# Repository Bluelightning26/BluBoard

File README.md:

# BluBoard
## A custom 75% keyboard!

### Key features: 
- MacOs Layout, 75% & separated arrow keys
- Two Rotary Encoders w/ Switches (Brightness + Volume)
- Cherry MX Brown Switches
- Simple Case with plop in design that keeps the black PCB visible while protecting the bottom and sides
- Specific parts used are documented in [BOM.md](BOM.md)

## Renders!!

### What I'd do differently next time
There were several sacrifices I had to make in the name of budgeting. Also, since this is my first full keyboard, I didn't want to overwhelm myself in the build process and avoided things that are difficult to solder. I am planning on making a v2 version of this keyboard after a few months of use, learning from the probable mistakes I made in design along the way

Nice features this would have:
- Wireless capability, BT + Dongle
- Acrylic Case
- RGB Backlit Keys
- 
(To be added to during build process along with when I use the board!)

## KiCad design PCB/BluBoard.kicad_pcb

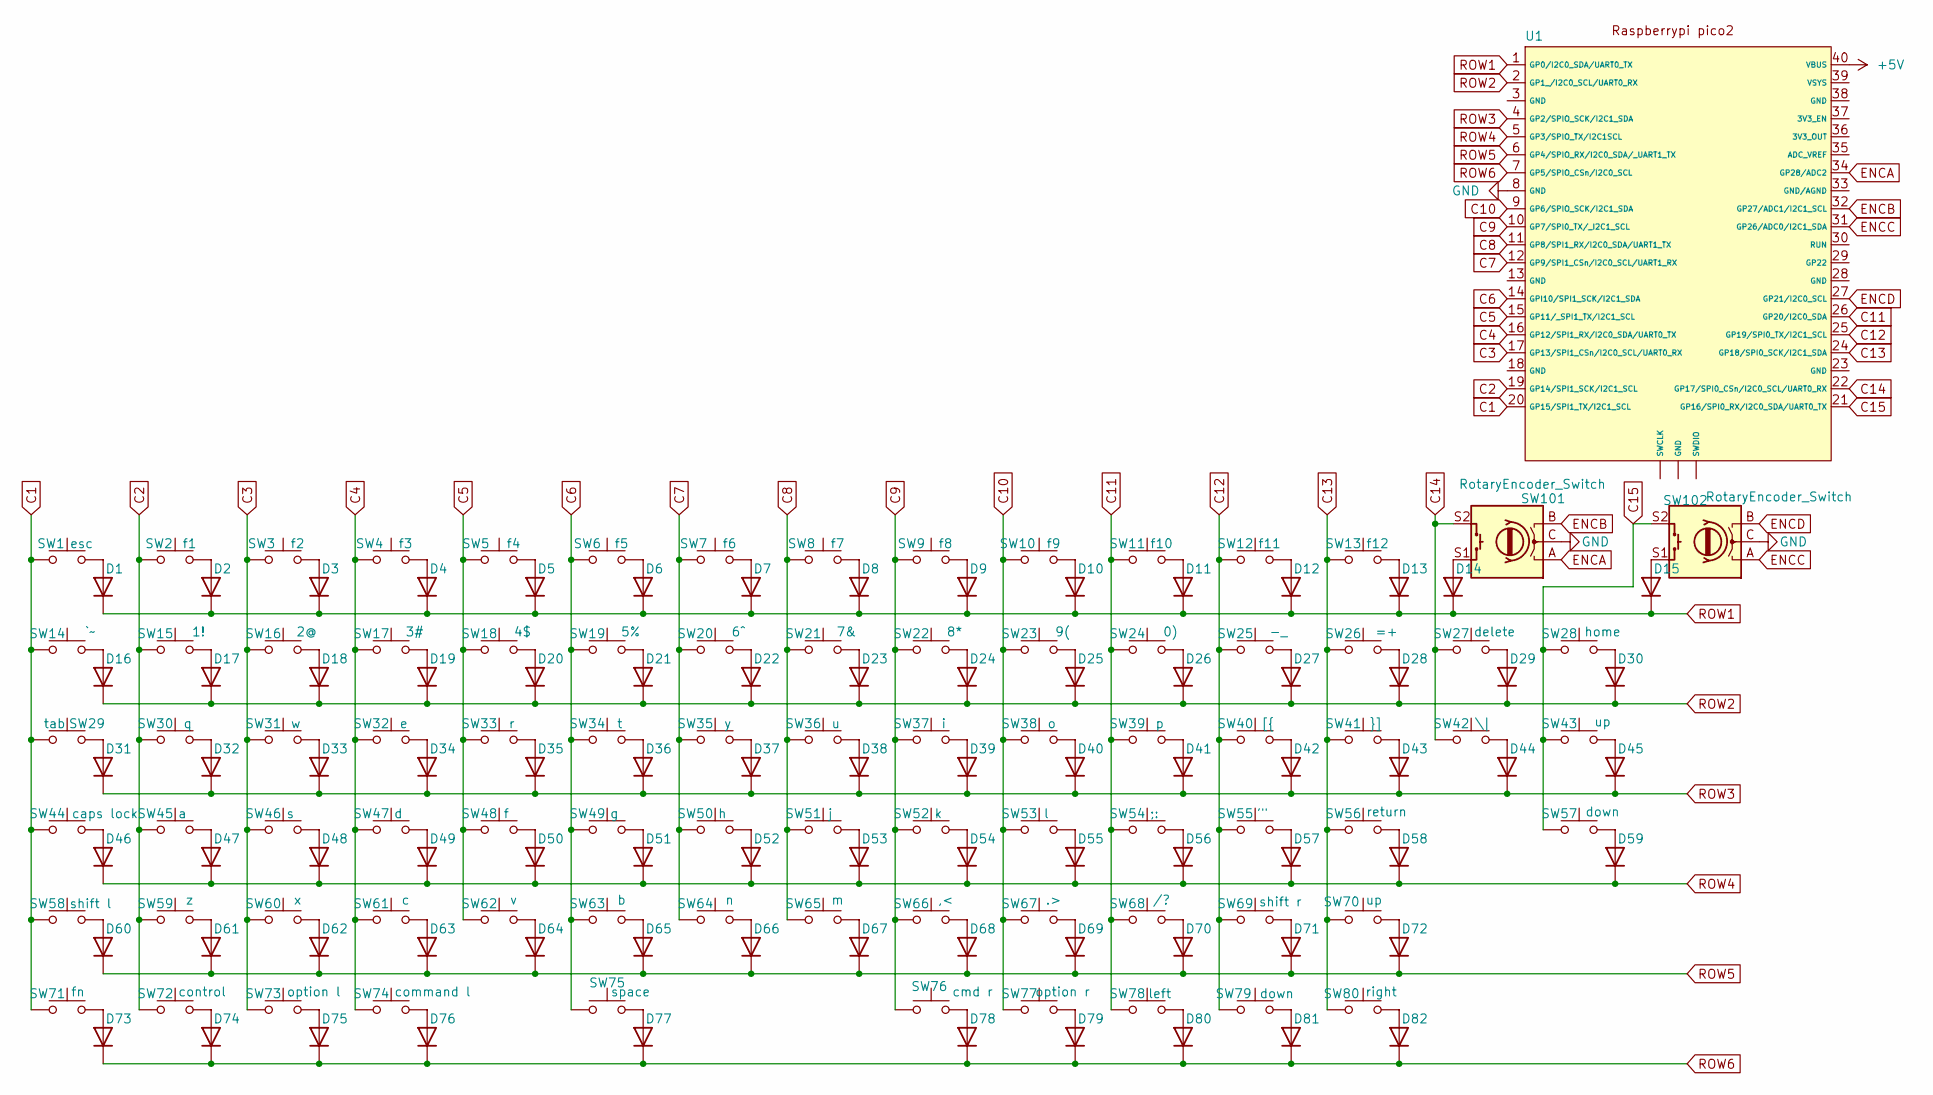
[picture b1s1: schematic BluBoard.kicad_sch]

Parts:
D1, D2, D3, D4, D5, D6, D7, D8, D9, D10, D11, D12, D13, D14, D15, D16, D17, D18, D19, D20, D21, D22, D23, D24, D25, D26, D27, D28, D29, D30, D31, D32, D33, D34, D35, D36, D37, D38, D39, D40, D41, D42, D43, D44, D45, D46, D47, D48, D49, D50, D51, D52, D53, D54, D55, D56, D57, D58, D59, D60, D61, D62, D63, D64, D65, D66, D67, D68, D69, D70, D71, D72, D73, D74, D75, D76, D77, D78, D79, D80, D81, D82: D; D_DO-35_SOD27_P7.62mm_Horizontal
SW1: esc; SW_Cherry_MX_1.00u_PCB
SW2: f1; SW_Cherry_MX_1.00u_PCB
SW3: f2; SW_Cherry_MX_1.00u_PCB
SW4: f3; SW_Cherry_MX_1.00u_PCB
SW5: f4; SW_Cherry_MX_1.00u_PCB
SW6: f5; SW_Cherry_MX_1.00u_PCB
SW7: f6; SW_Cherry_MX_1.00u_PCB
SW8: f7; SW_Cherry_MX_1.00u_PCB
SW9: f8; SW_Cherry_MX_1.00u_PCB
SW10: f9; SW_Cherry_MX_1.00u_PCB
SW11: f10; SW_Cherry_MX_1.00u_PCB
SW12: f11; SW_Cherry_MX_1.00u_PCB
SW13: f12; SW_Cherry_MX_1.00u_PCB
SW14: `~; SW_Cherry_MX_1.00u_PCB
SW15: 1!; SW_Cherry_MX_1.00u_PCB
SW16: 2@; SW_Cherry_MX_1.00u_PCB
SW17: 3#; SW_Cherry_MX_1.00u_PCB
SW18: 4$; SW_Cherry_MX_1.00u_PCB
SW19: 5%; SW_Cherry_MX_1.00u_PCB
SW20: 6^; SW_Cherry_MX_1.00u_PCB
SW21: 7&; SW_Cherry_MX_1.00u_PCB
SW22: 8*; SW_Cherry_MX_1.00u_PCB
SW23: 9(; SW_Cherry_MX_1.00u_PCB
SW24: 0); SW_Cherry_MX_1.00u_PCB
SW25: -_; SW_Cherry_MX_1.00u_PCB
SW26: =+; SW_Cherry_MX_1.00u_PCB
SW27: delete; SW_Cherry_MX_2.00u_PCB
SW28: home; SW_Cherry_MX_1.00u_PCB
SW29: tab; SW_Cherry_MX_1.50u_PCB
SW30: q; SW_Cherry_MX_1.00u_PCB
SW31: w; SW_Cherry_MX_1.00u_PCB
SW32: e; SW_Cherry_MX_1.00u_PCB
SW33: r; SW_Cherry_MX_1.00u_PCB
SW34: t; SW_Cherry_MX_1.00u_PCB
SW35: y; SW_Cherry_MX_1.00u_PCB
SW36: u; SW_Cherry_MX_1.00u_PCB
SW37: i; SW_Cherry_MX_1.00u_PCB
SW38: o; SW_Cherry_MX_1.00u_PCB
SW39: p; SW_Cherry_MX_1.00u_PCB
SW40: [{; SW_Cherry_MX_1.00u_PCB
SW41: }]; SW_Cherry_MX_1.00u_PCB
SW42: \|; SW_Cherry_MX_1.50u_PCB
SW43, SW70: up; SW_Cherry_MX_1.00u_PCB
SW44: caps lock; SW_Cherry_MX_1.75u_PCB
SW45: a; SW_Cherry_MX_1.00u_PCB
SW46: s; SW_Cherry_MX_1.00u_PCB
SW47: d; SW_Cherry_MX_1.00u_PCB
SW48: f; SW_Cherry_MX_1.00u_PCB
SW49: g; SW_Cherry_MX_1.00u_PCB
SW50: h; SW_Cherry_MX_1.00u_PCB
SW51: j; SW_Cherry_MX_1.00u_PCB
SW52: k; SW_Cherry_MX_1.00u_PCB
SW53: l; SW_Cherry_MX_1.00u_PCB
SW54: ;:; SW_Cherry_MX_1.00u_PCB
SW55: '"; SW_Cherry_MX_1.00u_PCB
SW56: return; SW_Cherry_MX_2.25u_PCB
SW57, SW79: down; SW_Cherry_MX_1.00u_PCB
SW58: shift l; SW_Cherry_MX_2.25u_PCB
SW59: z; SW_Cherry_MX_1.00u_PCB
SW60: x; SW_Cherry_MX_1.00u_PCB
SW61: c; SW_Cherry_MX_1.00u_PCB
SW62: v; SW_Cherry_MX_1.00u_PCB
SW63: b; SW_Cherry_MX_1.00u_PCB
SW64: n; SW_Cherry_MX_1.00u_PCB
SW65: m; SW_Cherry_MX_1.00u_PCB
SW66: ,<; SW_Cherry_MX_1.00u_PCB
SW67: .>; SW_Cherry_MX_1.00u_PCB
SW68: /?; SW_Cherry_MX_1.00u_PCB
SW69: shift r; SW_Cherry_MX_2.25u_PCB
SW71: fn; SW_Cherry_MX_1.00u_PCB
SW72: control; SW_Cherry_MX_1.00u_PCB
SW73: option l; SW_Cherry_MX_1.00u_PCB
SW74: command l; SW_Cherry_MX_1.25u_PCB
SW75: space; SW_Cherry_MX_6.25u_PCB
SW76: cmd r; SW_Cherry_MX_1.25u_PCB
SW77: option r; SW_Cherry_MX_1.00u_PCB
SW78: left; SW_Cherry_MX_1.00u_PCB
SW80: right; SW_Cherry_MX_1.00u_PCB
SW101, SW102: RotaryEncoder_Switch; RotaryEncoder_Alps_EC11E-Switch_Vertical_H20mm
U1: RaspberryPi_Pico_Common_THT

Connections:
+5V: U1.40 (VBUS)
C1: SW1.1, SW14.1, SW29.2, SW44.1, SW58.1, SW71.1, U1.20 (GP15/SPI1_TX/I2C1_SCL)
C2: SW2.1, SW15.1, SW30.1, SW45.1, SW59.1, SW72.1, U1.19 (GP14/SPI1_SCK/I2C1_SCL)
C3: SW3.1, SW16.1, SW31.1, SW46.1, SW60.1, SW73.1, U1.17 (GP13/SPI1_CSn/I2C0_SCL/UART0_RX)
C4: SW4.1, SW17.1, SW32.1, SW47.1, SW61.1, SW74.1, U1.16 (GP12/SPI1_RX/I2C0_SDA/UART0_TX)
C5: SW5.1, SW18.1, SW33.1, SW48.1, SW62.1, U1.15 (GP11/_SPI1_TX/I2C1_SCL)
C6: SW6.1, SW19.1, SW34.1, SW49.1, SW63.1, SW75.1, U1.14 (GPI10/SPI1_SCK/I2C1_SDA)
C7: SW7.1, SW20.1, SW35.1, SW50.1, SW64.1, U1.12 (GP9/SPI1_CSn/I2C0_SCL/UART1_RX)
C8: SW8.1, SW21.1, SW36.1, SW51.1, SW65.1, U1.11 (GP8/SPI1_RX/I2C0_SDA/UART1_TX)
C9: SW9.1, SW22.1, SW37.1, SW52.1, SW66.1, SW76.1, U1.10 (GP7/SPI0_TX/_I2C1_SCL)
C10: SW10.1, SW23.1, SW38.1, SW53.1, SW67.1, SW77.1, U1.9 (GP6/SPIO_SCK/I2C1_SDA)
C11: SW11.1, SW24.1, SW39.1, SW54.1, SW68.1, SW78.1, U1.26 (GP20/I2C0_SDA)
C12: SW12.1, SW25.1, SW40.1, SW55.1, SW69.1, SW79.1, U1.25 (GP19/SPI0_TX/I2C1_SCL)
C13: SW13.1, SW26.1, SW41.1, SW56.1, SW70.1, SW80.1, U1.24 (GP18/SPI0_SCK/I2C1_SDA)
C14: SW27.1, SW42.1, SW101.S2, U1.22 (GP17/SPI0_CSn/I2C0_SCL/UART0_RX)
C15: SW28.1, SW43.1, SW57.1, SW102.S2, U1.21 (GP16/SPI0_RX/I2C0_SDA/UART0_TX)
ENCA: SW101.A, U1.34 (GP28/ADC2)
ENCB: SW101.B, U1.32 (GP27/ADC1/I2C1_SCL)
ENCC: SW102.A, U1.31 (GP26/ADC0/I2C1_SDA)
ENCD: SW102.B, U1.27 (GP21/I2C0_SCL)
GND: SW101.C, SW102.C, U1.8 (GND)
unnamed: D1.2 (A), SW1.2
unnamed: D2.2 (A), SW2.2
unnamed: D3.2 (A), SW3.2
unnamed: D4.2 (A), SW4.2
unnamed: D5.2 (A), SW5.2
unnamed: D6.2 (A), SW6.2
unnamed: D7.2 (A), SW7.2
unnamed: D8.2 (A), SW8.2
unnamed: D9.2 (A), SW9.2
unnamed: D10.2 (A), SW10.2
unnamed: D11.2 (A), SW11.2
unnamed: D12.2 (A), SW12.2
unnamed: D13.2 (A), SW13.2
unnamed: D14.2 (A), SW101.S1
unnamed: D15.2 (A), SW102.S1
unnamed: D16.2 (A), SW14.2
unnamed: D17.2 (A), SW15.2
unnamed: D18.2 (A), SW16.2
unnamed: D19.2 (A), SW17.2
unnamed: D20.2 (A), SW18.2
unnamed: D21.2 (A), SW19.2
unnamed: D22.2 (A), SW20.2
unnamed: D23.2 (A), SW21.2
unnamed: D24.2 (A), SW22.2
unnamed: D25.2 (A), SW23.2
unnamed: D26.2 (A), SW24.2
unnamed: D27.2 (A), SW25.2
unnamed: D28.2 (A), SW26.2
unnamed: D29.2 (A), SW27.2
unnamed: D30.2 (A), SW28.2
unnamed: D31.2 (A), SW29.1
unnamed: D32.2 (A), SW30.2
unnamed: D33.2 (A), SW31.2
unnamed: D34.2 (A), SW32.2
unnamed: D35.2 (A), SW33.2
unnamed: D36.2 (A), SW34.2
unnamed: D37.2 (A), SW35.2
unnamed: D38.2 (A), SW36.2
unnamed: D39.2 (A), SW37.2
unnamed: D40.2 (A), SW38.2
unnamed: D41.2 (A), SW39.2
unnamed: D42.2 (A), SW40.2
unnamed: D43.2 (A), SW41.2
unnamed: D44.2 (A), SW42.2
unnamed: D45.2 (A), SW43.2
unnamed: D46.2 (A), SW44.2
unnamed: D47.2 (A), SW45.2
unnamed: D48.2 (A), SW46.2
unnamed: D49.2 (A), SW47.2
unnamed: D50.2 (A), SW48.2
unnamed: D51.2 (A), SW49.2
unnamed: D52.2 (A), SW50.2
unnamed: D53.2 (A), SW51.2
unnamed: D54.2 (A), SW52.2
unnamed: D55.2 (A), SW53.2
unnamed: D56.2 (A), SW54.2
unnamed: D57.2 (A), SW55.2
unnamed: D58.2 (A), SW56.2
unnamed: D59.2 (A), SW57.2
unnamed: D60.2 (A), SW58.2
unnamed: D61.2 (A), SW59.2
unnamed: D62.2 (A), SW60.2
unnamed: D63.2 (A), SW61.2
unnamed: D64.2 (A), SW62.2
unnamed: D65.2 (A), SW63.2
unnamed: D66.2 (A), SW64.2
unnamed: D67.2 (A), SW65.2
unnamed: D68.2 (A), SW66.2
unnamed: D69.2 (A), SW67.2
unnamed: D70.2 (A), SW68.2
unnamed: D71.2 (A), SW69.2
unnamed: D72.2 (A), SW70.2
unnamed: D73.2 (A), SW71.2
unnamed: D74.2 (A), SW72.2
unnamed: D75.2 (A), SW73.2
unnamed: D76.2 (A), SW74.2
unnamed: D77.2 (A), SW75.2
unnamed: D78.2 (A), SW76.2
unnamed: D79.2 (A), SW77.2
unnamed: D80.2 (A), SW78.2
unnamed: D81.2 (A), SW79.2
unnamed: D82.2 (A), SW80.2
ROW1: D1.1 (K), D2.1 (K), D3.1 (K), D4.1 (K), D5.1 (K), D6.1 (K), D7.1 (K), D8.1 (K), D9.1 (K), D10.1 (K), D11.1 (K), D12.1 (K), D13.1 (K), D14.1 (K), D15.1 (K), U1.1 (GP0/I2C0_SDA/UART0_TX)
ROW2: D16.1 (K), D17.1 (K), D18.1 (K), D19.1 (K), D20.1 (K), D21.1 (K), D22.1 (K), D23.1 (K), D24.1 (K), D25.1 (K), D26.1 (K), D27.1 (K), D28.1 (K), D29.1 (K), D30.1 (K), U1.2 (GP1_/I2C0_SCL/UART0_RX)
ROW3: D31.1 (K), D32.1 (K), D33.1 (K), D34.1 (K), D35.1 (K), D36.1 (K), D37.1 (K), D38.1 (K), D39.1 (K), D40.1 (K), D41.1 (K), D42.1 (K), D43.1 (K), D44.1 (K), D45.1 (K), U1.4 (GP2/SPIO_SCK/I2C1_SDA)
ROW4: D46.1 (K), D47.1 (K), D48.1 (K), D49.1 (K), D50.1 (K), D51.1 (K), D52.1 (K), D53.1 (K), D54.1 (K), D55.1 (K), D56.1 (K), D57.1 (K), D58.1 (K), D59.1 (K), U1.5 (GP3/SPIO_TX/I2C1SCL)
ROW5: D60.1 (K), D61.1 (K), D62.1 (K), D63.1 (K), D64.1 (K), D65.1 (K), D66.1 (K), D67.1 (K), D68.1 (K), D69.1 (K), D70.1 (K), D71.1 (K), D72.1 (K), U1.6 (GP4/SPIO_RX/I2C0_SDA/_UART1_TX)
ROW6: D73.1 (K), D74.1 (K), D75.1 (K), D76.1 (K), D77.1 (K), D78.1 (K), D79.1 (K), D80.1 (K), D81.1 (K), D82.1 (K), U1.7 (GP5/SPIO_CSn/I2C0_SCL)

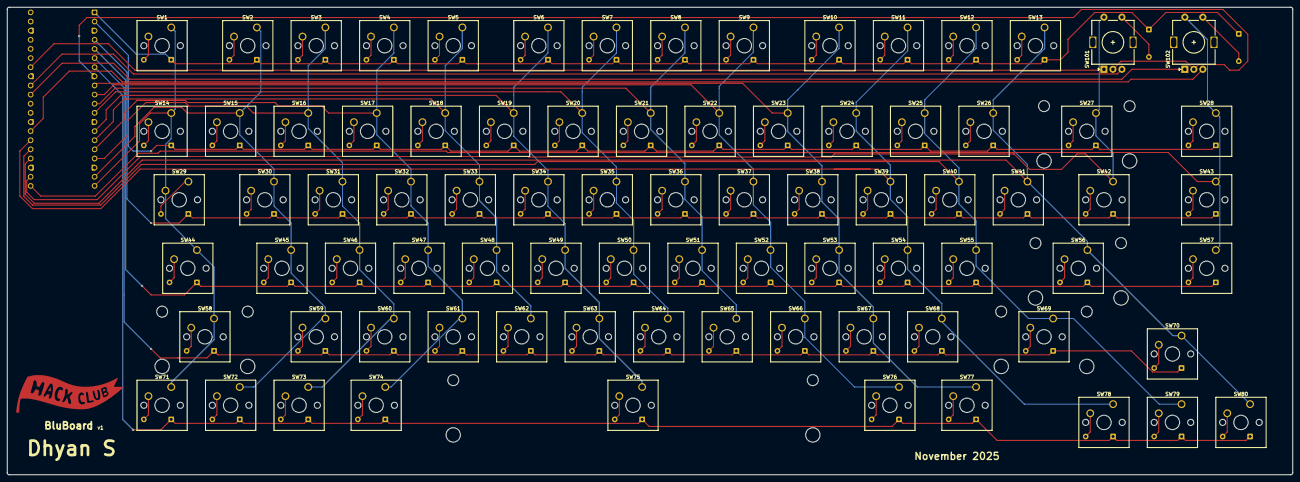
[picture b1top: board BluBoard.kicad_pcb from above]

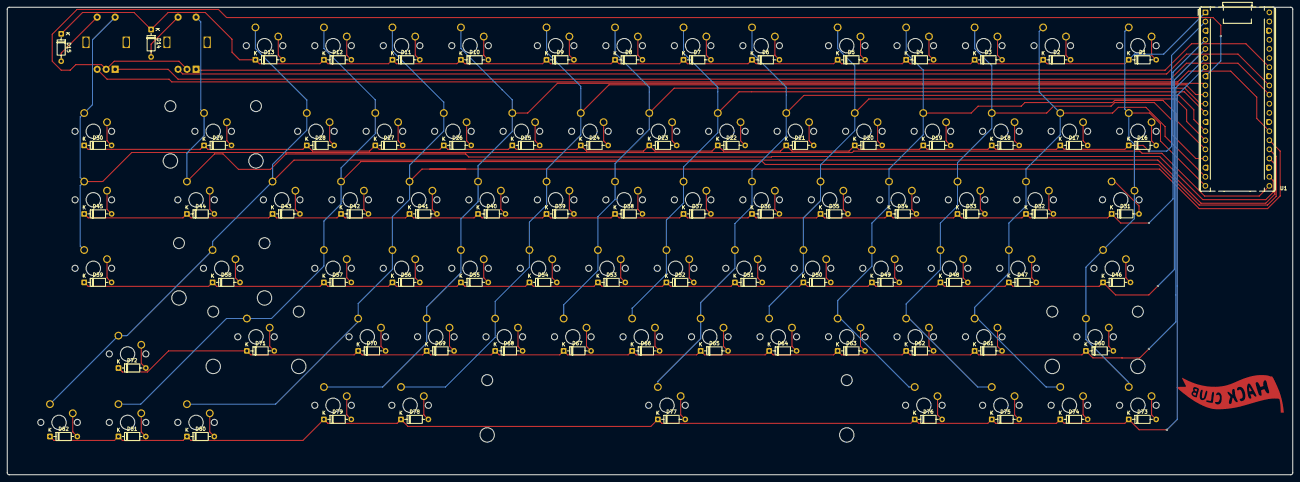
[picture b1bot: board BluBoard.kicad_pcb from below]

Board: 2 copper layers, 357.5 x 130.0 mm, 165 parts (83 on the bottom side), 108 nets.

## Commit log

2025-11-30 yay!
